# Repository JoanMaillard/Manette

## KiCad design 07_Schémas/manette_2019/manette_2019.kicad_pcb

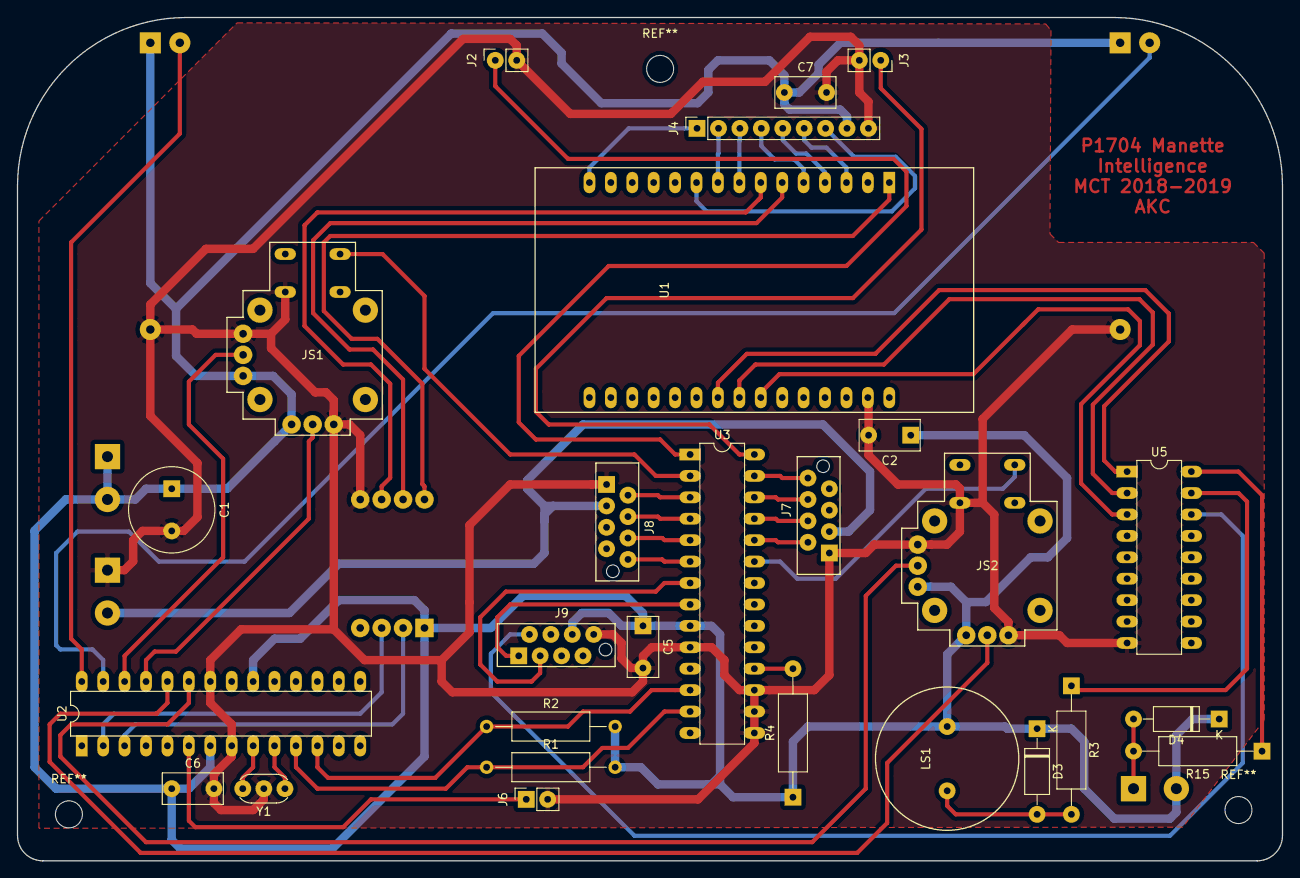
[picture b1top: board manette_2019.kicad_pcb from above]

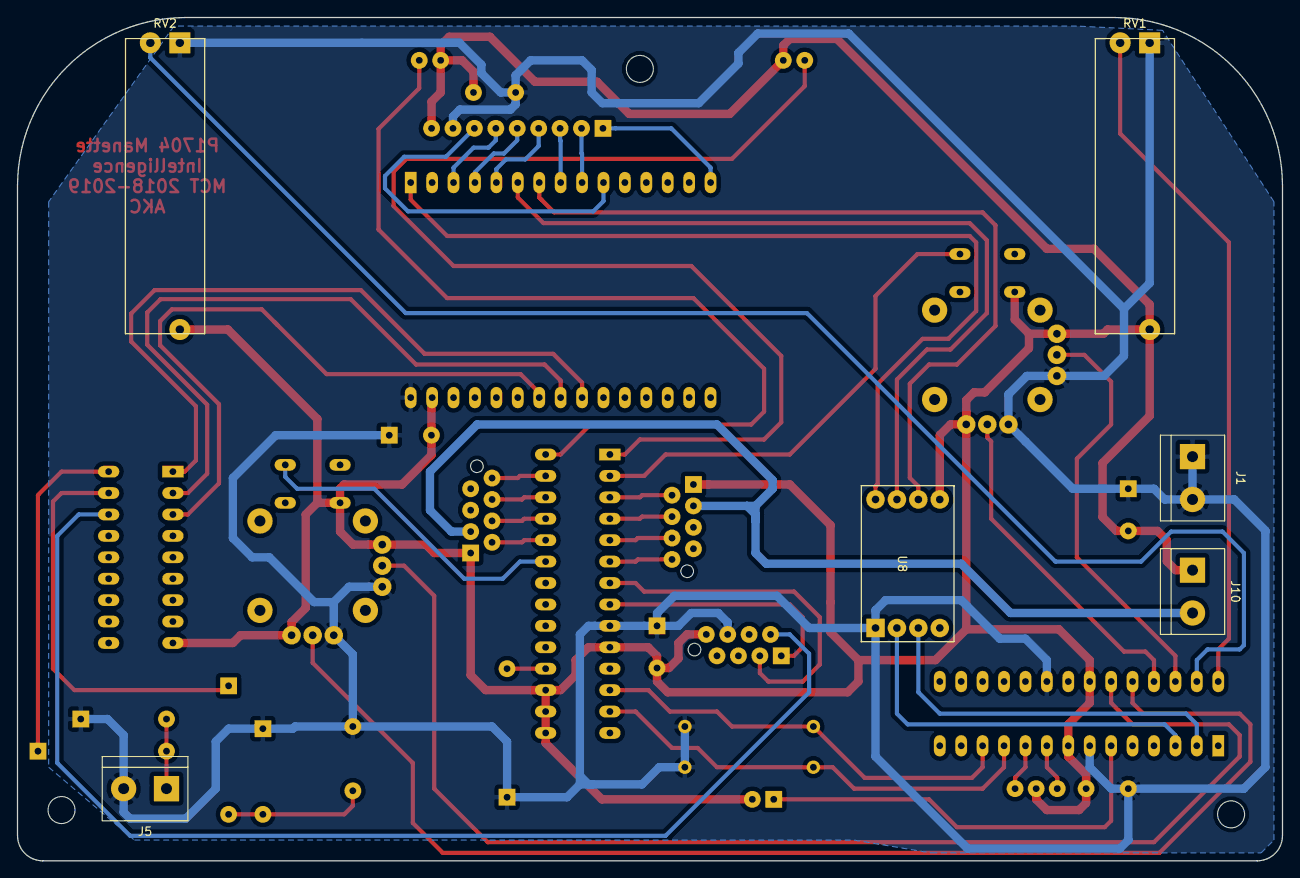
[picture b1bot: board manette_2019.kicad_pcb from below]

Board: 2 copper layers, 150.0 x 100.0 mm, 33 parts (6 on the bottom side), 49 nets.

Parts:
C1: C; C_Radial_D10.0mm_H20.0mm_P5.00mm
C2, C5, C6, C7: C; C_Rect_L7.0mm_W3.5mm_P5.00mm
D3, D4: D; D_A-405_P10.16mm_Horizontal
J1: Vcc; TerminalBlock_bornier-2_P5.08mm
J2: L_Bumper; PinSocket_1x02_P2.54mm_Vertical
J3: R_Bumper; PinSocket_1x02_P2.54mm_Vertical
J4: OLED_Display; PinSocket_1x09_P2.54mm_Vertical
J5: Rumble; TerminalBlock_bornier-2_P5.08mm
J6: Calib; PinSocket_1x02_P2.54mm_Vertical
J7: Conn_R_Button; Conn_8
J8: Conn_L_Button; Conn_8
J9: Conn_Middle_PCB; Conn_8
J10: Alim_LED; TerminalBlock_bornier-2_P5.08mm
JS1: Joystick_Left; Joystick_RSF_2-axis
JS2: Joystick_Right; Joystick_RSF_2-axis
LS1: Speaker; Buzzer_T135
R1, R2, R3, R4, R15: R; R_Axial_DIN0309_L9.0mm_D3.2mm_P15.24mm_Horizontal
RV1: L_POT; Potentiomètre linéaire
RV2: R_POT; Potentiomètre linéaire
U1: ESP32
U2: ATmega328-PU; DIP-28_W7.62mm
U3: MCP23017; DIP-28_W7.62mm
U5: ULN2803A; DIP-18_W7.62mm
U8: PCA9306
Y1: Resonator; Resonator-3Pin_W6.0mm_H3.0mm

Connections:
+3.3V: U1.1, U8.8
+5V: C1.1, C2.1, C5.1, C6.1, C7.1, D3.1, D4.1, J1.1, J1.2, J4.8, J5.2, J9.6, JS1.1, JS1.4, JS2.1, JS2.4, LS1.2, R1.2, R2.2, R4.1, RV1.1, RV2.1, U1.30, U2.7, U2.20, U3.9, U8.1
Button_A: J7.2, U3.24
Button_B: J7.8, U3.27
Button_DOWN: J8.6, U3.5
Button_LEFT: J8.8, U3.6
Button_RIGHT: J8.4, U3.4
Button_SELECT: J9.1, U3.8
Button_START: J9.3, U3.7
Button_UP: J8.2, U3.3
Button_X: J7.4, U3.25
Button_Y: J7.6, U3.26
Buzzer: U1.23, U5.2
Calib: J6.1, U2.6
Conn_LED_On: J9.2, U5.16
Connected: U1.24, U5.3
DC: J4.3, U1.8
GND: C1.2, C2.2, C5.2, C6.2, C7.2, J2.2, J3.2, J4.9, J6.2, J7.1, J8.1, J9.8, J10.1, JS1.3, JS1.6, JS1.9, JS2.3, JS2.6, JS2.9, RV1.3, RV2.3, U1.29, U2.8, U2.22, U3.10, U3.15, U3.16, U3.17, U5.9, U8.5, Y1.2
L_Bumper: J2.1, U3.1
L_joystick_analog_x: JS1.2, U2.26
L_joystick_analog_y: JS1.5, U2.25
L_trigger: RV1.2, U2.28
Left_joystick_button: JS1.8, U3.2
MISO: J4.7, U1.10
MOSI: J4.1, U1.15
unnamed: D3.2, LS1.1, R3.2
unnamed: D4.2, J5.1, R15.2
unnamed: R3.1, U5.17
unnamed: R4.2, U3.18
unnamed: R15.1, U5.18
unnamed: U2.9, Y1.3
unnamed: U2.10, Y1.1
OLEDCS: J4.5, U1.4
RESET: J4.4, U1.5
RX_Atmega: U2.2, U8.3
RX_ESP32: U1.6, U8.7
R_Bumper: J3.1, U3.28
R_joystick_analog_x: JS2.2, U2.23
R_joystick_analog_y: JS2.5, U2.24
R_trigger: RV2.2, U2.27
Right_joystick_button: JS2.8, U3.23
Rumble: U1.22, U5.1
SCK: J4.2, U1.9
SCL: R2.1, U2.12, U3.12
SDA: R1.1, U2.11, U3.13
SDCS: J4.6, U1.3
TX_Atmega: U2.3, U8.2
TX_ESP32: U1.7, U8.6
VCC_LED: J7.3, J8.3, J10.2

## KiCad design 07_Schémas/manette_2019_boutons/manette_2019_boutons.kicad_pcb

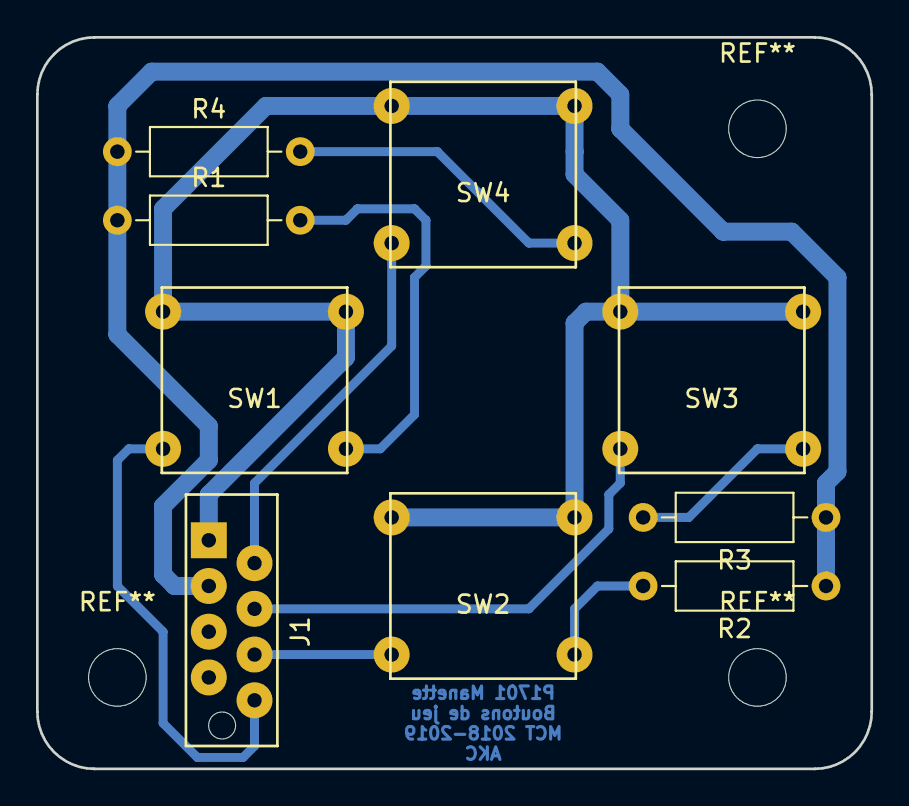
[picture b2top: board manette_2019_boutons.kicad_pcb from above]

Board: 2 copper layers, 46.4 x 40.6 mm, 9 parts (0 on the bottom side), 10 nets.

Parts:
J1: Conn_bouton; Conn_8
R1, R2, R3, R4: R; R_Axial_DIN0207_L6.3mm_D2.5mm_P10.16mm_Horizontal
SW1: Bouton_1; Bouton_MEC
SW2: Bouton_2; Bouton_MEC
SW3: Bouton_3; Bouton_MEC
SW4: Bouton_4; Bouton_MEC

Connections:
Bouton_Bas: J1.6, SW2.4
Bouton_Droite: J1.4, SW3.4
Bouton_Gauche: J1.8, SW1.4
Bouton_Haut: J1.2, SW4.4
GND: J1.1, SW1.1, SW1.2, SW2.1, SW2.2, SW3.1, SW3.2, SW4.1, SW4.2
unnamed: R1.2, SW1.3
unnamed: R2.2, SW2.3
unnamed: R3.2, SW3.3
unnamed: R4.2, SW4.3
Vcc_LED: J1.3, R1.1, R2.1, R3.1, R4.1

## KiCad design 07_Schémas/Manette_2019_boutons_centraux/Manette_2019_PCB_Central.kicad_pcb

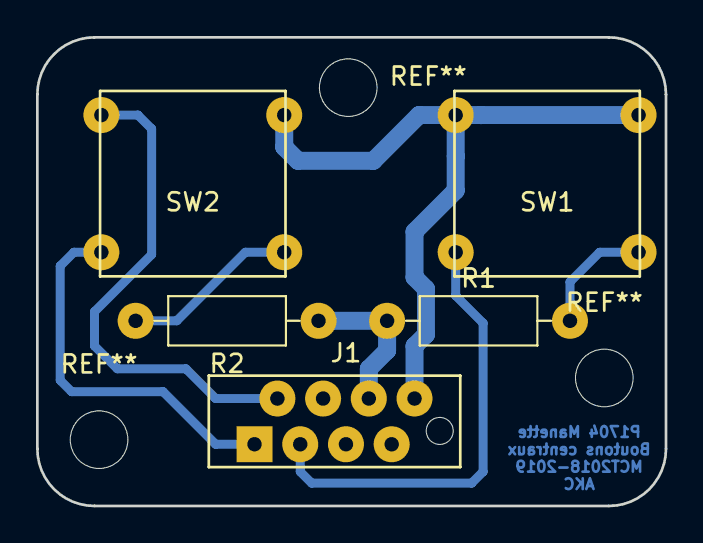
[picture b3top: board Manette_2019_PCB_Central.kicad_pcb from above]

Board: 2 copper layers, 34.9 x 26.0 mm, 5 parts (0 on the bottom side), 7 nets.

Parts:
J1: Conn_Middle_PCB; Conn_8
R1, R2: R; R_Axial_DIN0207_L6.3mm_D2.5mm_P10.16mm_Horizontal
SW1: Button_Start; Bouton_MEC
SW2: Button_Select; Bouton_MEC

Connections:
+5V: J1.6, R1.1, R2.1
Conn_LED_On: J1.2, SW2.2
GND: J1.8, SW1.1, SW1.2, SW2.1
unnamed: R1.2, SW1.3
unnamed: R2.2, SW2.3
button_SELECT: J1.1, SW2.4
button_START: J1.3, SW1.4

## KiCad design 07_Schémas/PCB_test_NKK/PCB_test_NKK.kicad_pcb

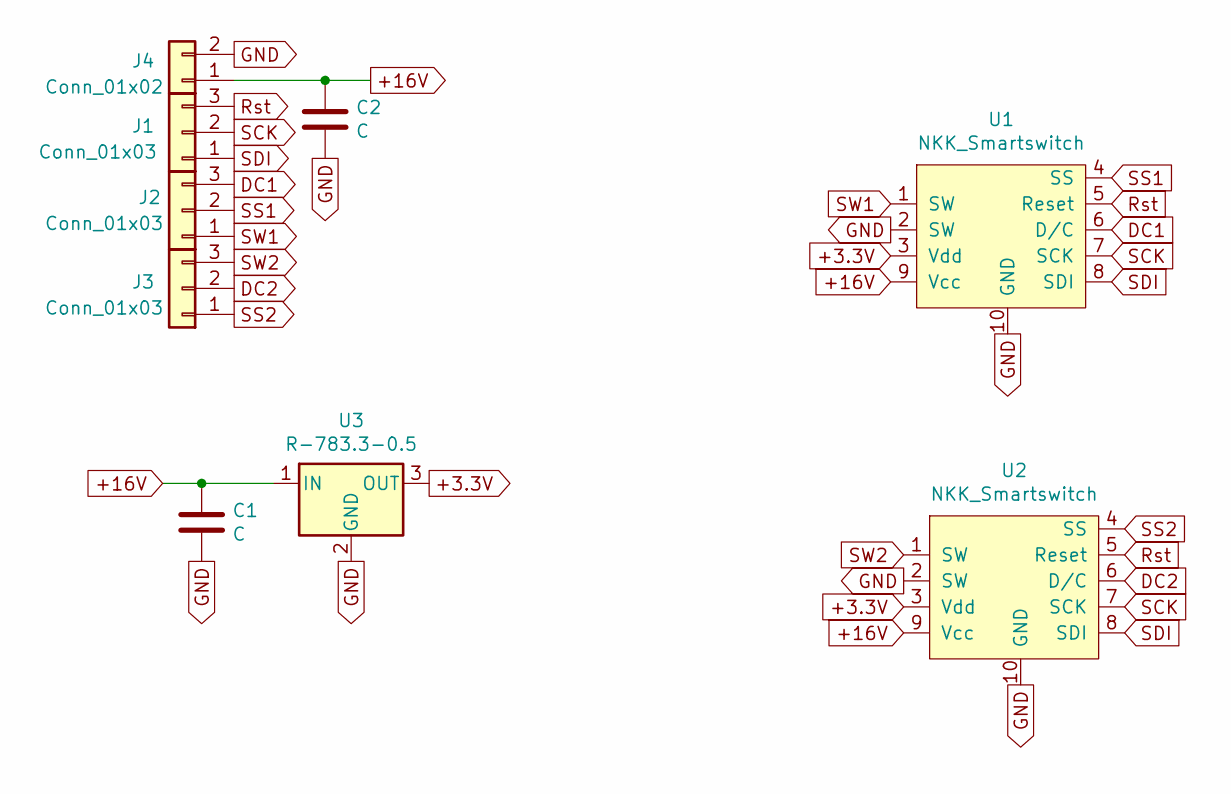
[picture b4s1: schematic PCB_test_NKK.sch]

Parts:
C1: C; C_Rect_L7.2mm_W3.5mm_P5.00mm_FKS2_FKP2_MKS2_MKP2
C2: C; CP_Radial_D10.0mm_P5.00mm
J1, J2, J3: Conn_01x03; TerminalBlock_Phoenix_MPT-0,5-3-2.54_1x03_P2.54mm_Horizontal
J4: Conn_01x02; TerminalBlock_Phoenix_MPT-0,5-2-2.54_1x02_P2.54mm_Horizontal
U1, U2: NKK_Smartswitch; NKK_Switch
U3: R-783.3-0.5; Converter_DCDC_RECOM_R-78E-0.5_THT

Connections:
+3.3V: U1.3 (Vdd), U2.3 (Vdd), U3.3 (OUT)
+16V: C1.1, C2.1, J4.1, U1.9 (Vcc), U2.9 (Vcc), U3.1 (IN)
DC1: J2.3, U1.6 (D/C)
DC2: J3.2, U2.6 (D/C)
GND: C1.2, C2.2, J4.2, U1.2 (SW), U1.10 (GND), U2.2 (SW), U2.10 (GND), U3.2 (GND)
Rst: J1.3, U1.5 (Reset), U2.5 (Reset)
SCK: J1.2, U1.7 (SCK), U2.7 (SCK)
SDI: J1.1, U1.8 (SDI), U2.8 (SDI)
SS1: J2.2, U1.4 (SS)
SS2: J3.1, U2.4 (SS)
SW1: J2.1, U1.1 (SW)
SW2: J3.3, U2.1 (SW)

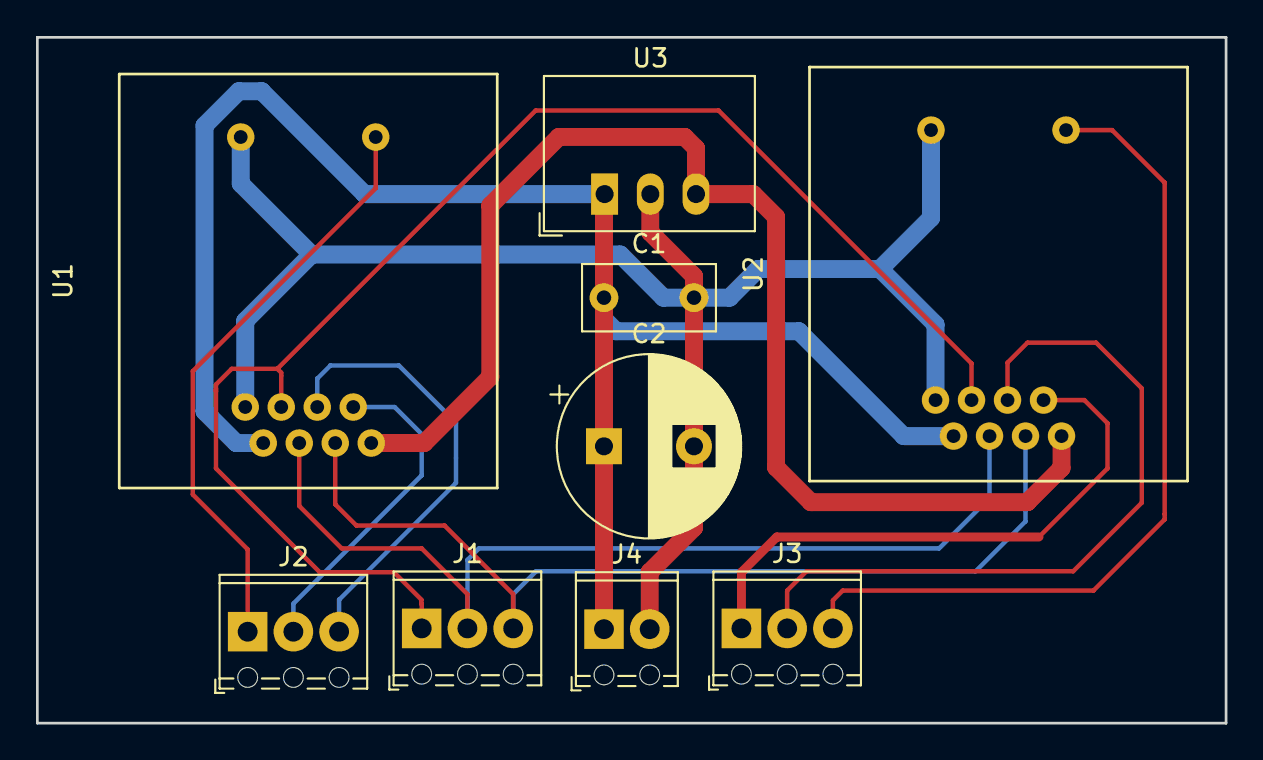
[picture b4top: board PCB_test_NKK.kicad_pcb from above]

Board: 2 copper layers, 66.0 x 38.1 mm, 9 parts (0 on the bottom side), 12 nets.

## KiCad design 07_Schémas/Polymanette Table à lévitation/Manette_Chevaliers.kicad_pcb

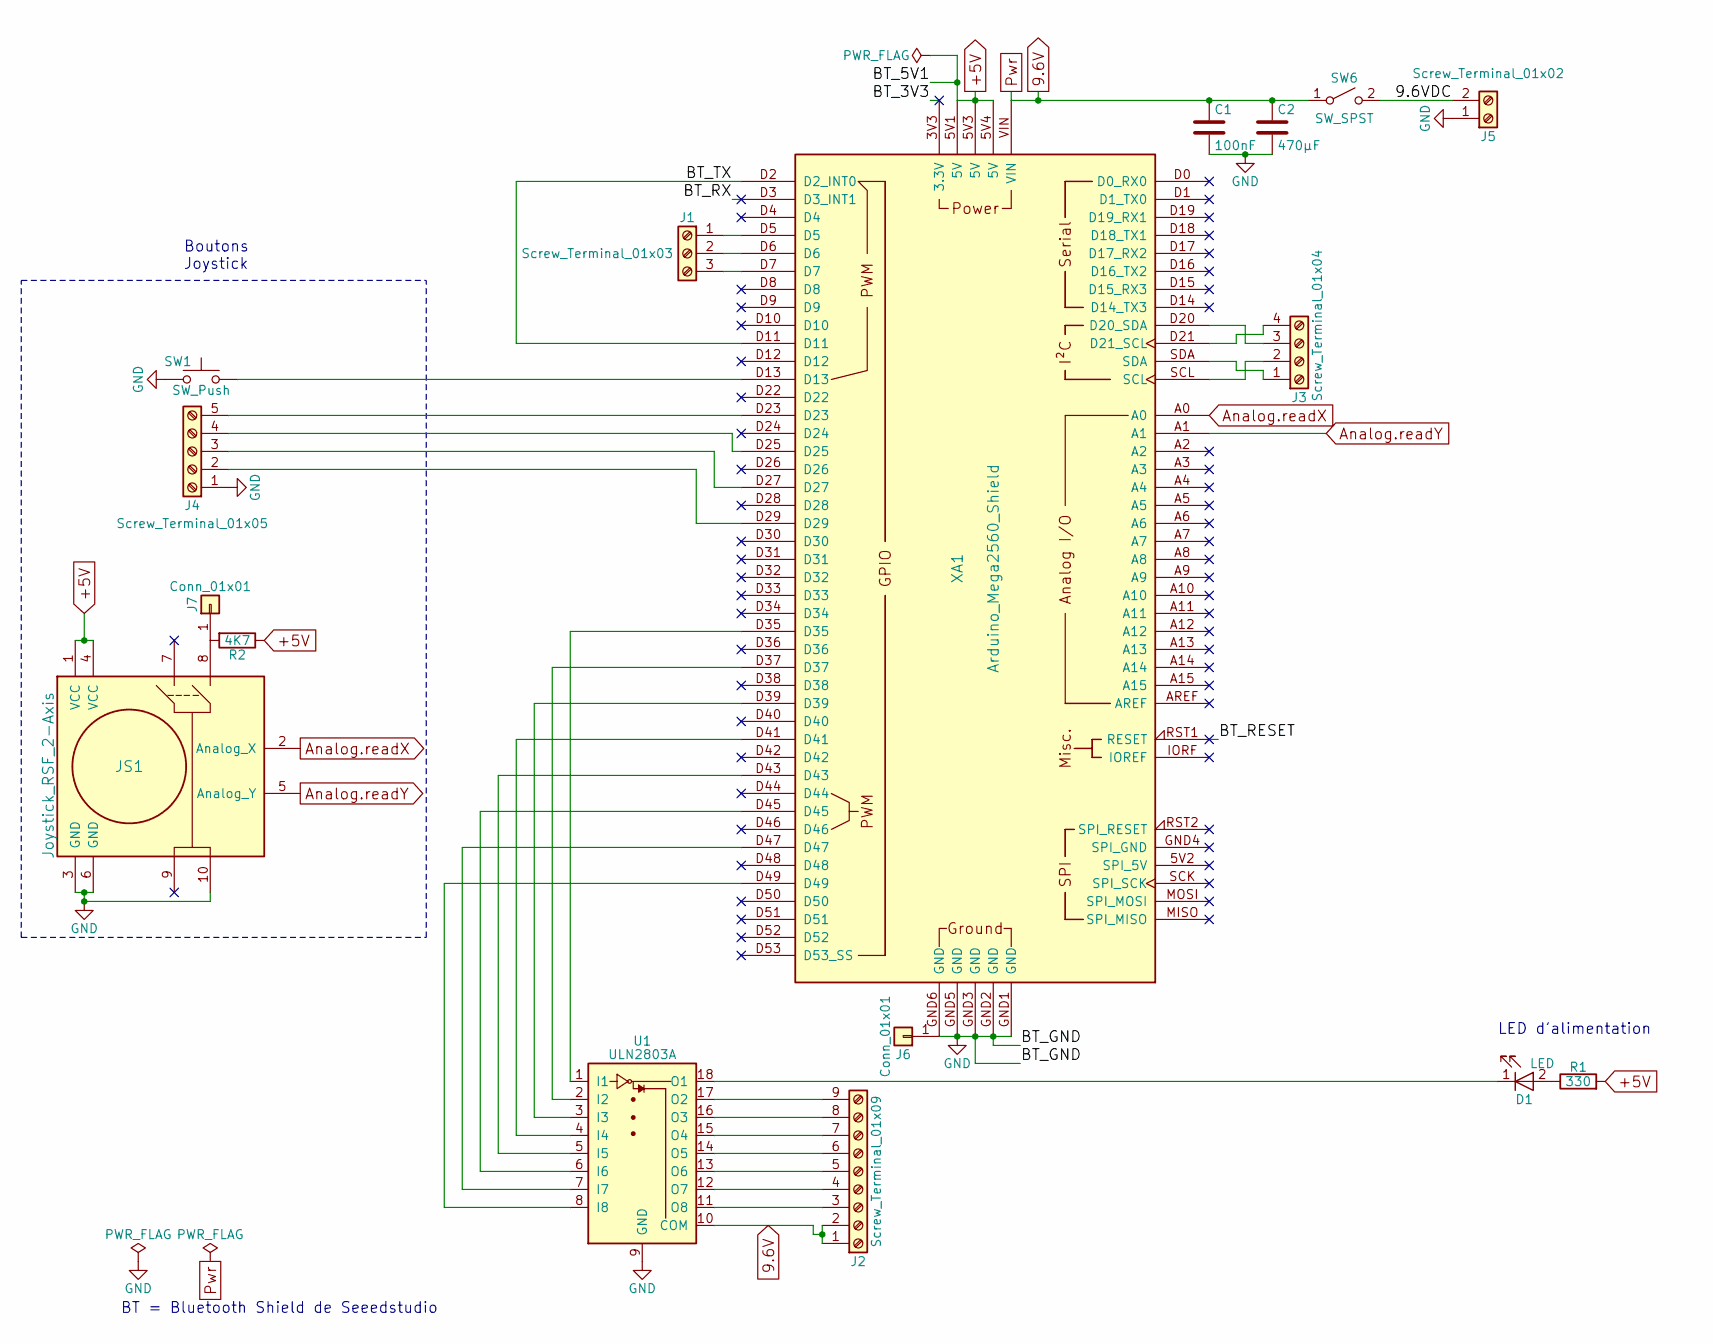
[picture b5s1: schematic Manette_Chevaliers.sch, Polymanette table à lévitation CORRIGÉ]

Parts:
C1: 100nF; C_Rect_L7.2mm_W2.5mm_P5.00mm_FKS2_FKP2_MKS2_MKP2
C2: 470µF; CP_Radial_Couchée_D10.0mm_P5.00mm
D1: LED; LED_D3.0mm
J1: Screw_Terminal_01x03; Screw_terminal_3_P2.54mm
J2: Screw_Terminal_01x09; Screw_terminal_3x3_P2.54mm
J3: Screw_Terminal_01x04; Screw_terminal_2x2_P2.54mm
J4: Screw_Terminal_01x05; Screw_terminal_2x3_P2.54mm
J5: Screw_Terminal_01x02; TerminalBlock_bornier-2_P5.08mm
J6, J7: Conn_01x01; Pad
JS1: Joystick_RSF_2-Axis; Joystick_RSF_2-axis
R1: 330; R_Axial_DIN0207_L6.3mm_D2.5mm_P10.16mm_Horizontal
R2: 4K7; R_Axial_DIN0207_L6.3mm_D2.5mm_P10.16mm_Horizontal
SW1: SW_Push; Switch_AS11CH
SW6: SW_SPST; Switch_AS11CH
U1: ULN2803A; ULN2803a
XA1: Arduino_Mega2560_Shield

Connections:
9.6V: C1.1, C2.1, J2.1, J2.2, SW6.1 (A), U1.10 (COM), XA1.VIN
+5V: JS1.1 (VCC), JS1.4 (VCC), R1.2, R2.1, XA1.5V1 (5V), XA1.5V3 (5V), XA1.5V4 (5V)
/9.6VDC: J5.2, SW6.2 (B)
/BT_3V3: XA1.3V3 (3.3V)
/BT_RESET: XA1.RST1 (RESET)
/BT_RX: XA1.D3 (D3_INT1)
/BT_TX: XA1.D2 (D2_INT0), XA1.D11
Analog.readX: JS1.2 (Analog_X), XA1.A0
Analog.readY: JS1.5 (Analog_Y), XA1.A1
GND: C1.2, C2.2, J4.1, J5.1, J6.1, JS1.3 (GND), JS1.6 (GND), JS1.10, SW1.2, U1.9 (GND), XA1.GND1 (GND), XA1.GND2 (GND), XA1.GND3 (GND), XA1.GND5 (GND), XA1.GND6 (GND)
unnamed: D1.1 (K), U1.18 (O1)
unnamed: D1.2 (A), R1.1
unnamed: J1.1, XA1.D5
unnamed: J1.2, XA1.D6
unnamed: J1.3, XA1.D7
unnamed: J2.3, U1.11 (O8)
unnamed: J2.4, U1.12 (O7)
unnamed: J2.5, U1.13 (O6)
unnamed: J2.6, U1.14 (O5)
unnamed: J2.7, U1.15 (O4)
unnamed: J2.8, U1.16 (O3)
unnamed: J2.9, U1.17 (O2)
unnamed: J3.1, XA1.SDA
unnamed: J3.2, XA1.SCL
unnamed: J3.3, XA1.D20 (D20_SDA)
unnamed: J3.4, XA1.D21 (D21_SCL)
unnamed: J4.2, XA1.D29
unnamed: J4.3, XA1.D27
unnamed: J4.4, XA1.D25
unnamed: J4.5, XA1.D23
unnamed: J7.1, JS1.8, R2.2
unnamed: SW1.1, XA1.D13
unnamed: U1.1 (I1), XA1.D35
unnamed: U1.2 (I2), XA1.D37
unnamed: U1.3 (I3), XA1.D39
unnamed: U1.4 (I4), XA1.D41
unnamed: U1.5 (I5), XA1.D43
unnamed: U1.6 (I6), XA1.D45
unnamed: U1.7 (I7), XA1.D47
unnamed: U1.8 (I8), XA1.D49

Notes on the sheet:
Boutons Joystick
BT = Bluetooth Shield de Seeedstudio
LED d'alimentation

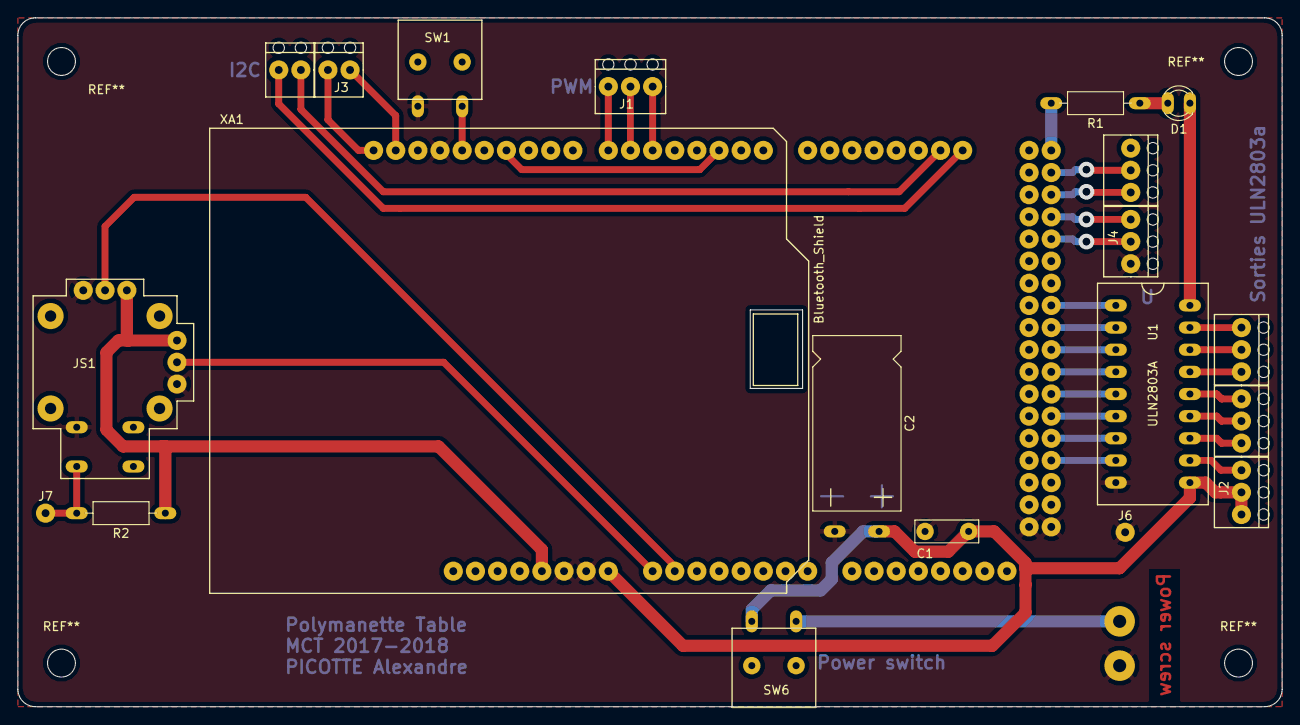
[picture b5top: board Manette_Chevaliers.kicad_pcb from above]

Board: 2 copper layers, 145.0 x 79.0 mm, 17 parts (1 on the bottom side), 37 nets.

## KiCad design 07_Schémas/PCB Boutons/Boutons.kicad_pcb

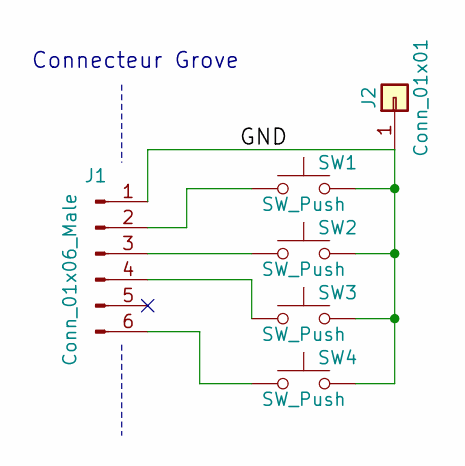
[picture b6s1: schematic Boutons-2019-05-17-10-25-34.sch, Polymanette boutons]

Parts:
J1: Conn_01x06_Male; Conn_Grove_6_pôles
J2: Conn_01x01; Pad
SW1, SW2, SW3, SW4: SW_Push; Switch_D6R

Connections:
/GND: J1.1, J2.1, SW1.2, SW2.2, SW3.2, SW4.2
unnamed: J1.2, SW1.1
unnamed: J1.3, SW2.1
unnamed: J1.4, SW3.1
unnamed: J1.6, SW4.1

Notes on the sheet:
Connecteur Grove

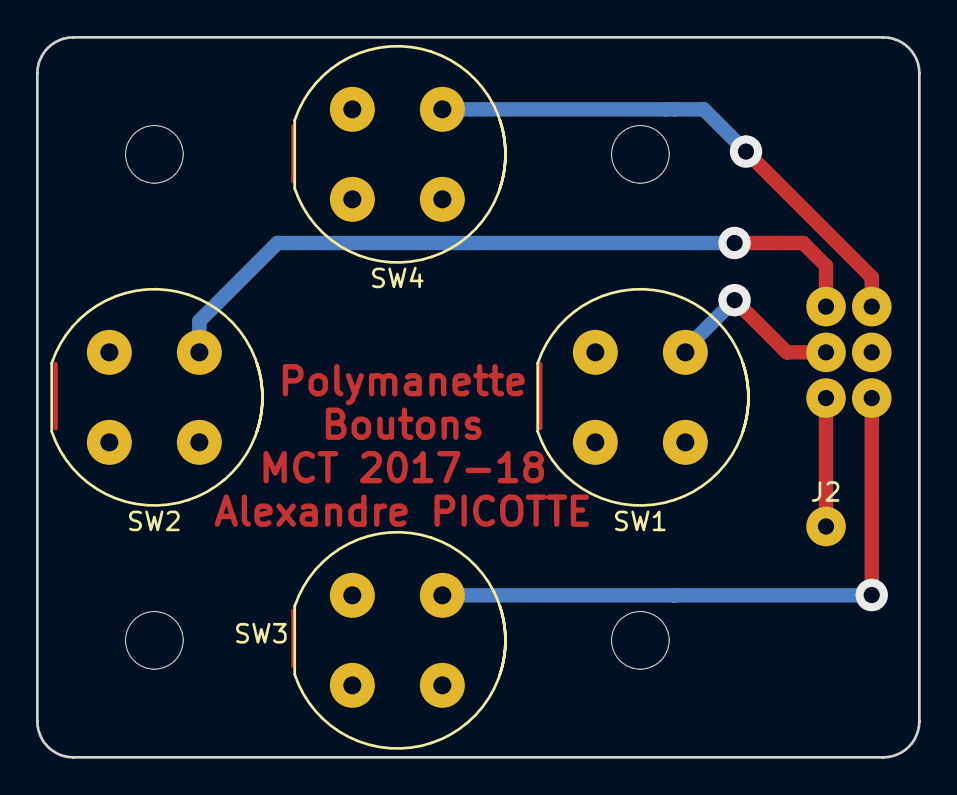
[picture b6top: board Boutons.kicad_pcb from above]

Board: 2 copper layers, 49.0 x 40.0 mm, 6 parts (1 on the bottom side), 5 nets.

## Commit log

2019-03-04 Initial commit
    Initial commit
2019-03-04 added résumé
    asdf
2019-03-04 schéma
2019-03-05 Code for serial communication testing
2019-03-05 Update journal, update MSProject sheet
2019-03-07 update schéma
2019-03-07 schéma update
2019-03-07 test code modified
    New code for 2 buttons and 1 potentiometer through Serial
2019-03-07 Optimization of test code (8 buttons to 1 byte)
2019-03-07 powerpoint
2019-03-07 update data rate test code
2019-03-07 Started schéma pour le test bench, cahier des charges
2019-03-11 update project file, receiver
2019-03-11 Cahier des charges
2019-03-11 update txt cahier des charges, plan projet MS Project
2019-03-12 added BT + PJON test code, doc refs, sub-diagram for BT comm
2019-03-12 Merge-fix commit
2019-03-12 Update plan de projet
2019-03-14 Cahier des charges intergroupe; save as XML des documents word
2019-03-14 Converted word documents to html
2019-03-14 Redo last
2019-03-15 docx update
2019-03-19 Update test_serial_sender.ino
    Added calibration routine
2019-03-21 Added per-direction calibration for good axis centering
2019-03-22 correct esp device names
2019-03-22 changes to comm code
2019-03-25 update MSP
2019-03-25 schema
2019-03-25 file movement
2019-03-25 update schema
2019-03-25 update code BT - working copy
2019-03-26 update BT code, journal, résumé
2019-03-26 ble code
2019-03-26 update code ESP for BT 33Hz
2019-03-26 Included serial receiver into BLE transmission
2019-03-28 Added two-way on BLE; sub-diagram update
2019-03-28 update receiver side
2019-04-01 update programmes
2019-04-02 update codes divers
2019-04-02 program corrections
2019-04-02 server and receiver change
2019-04-04 Update plan_projet_manette_2019.mpp
    quelques modifs à faire possiblement
2019-04-04 Update server code for latency reduction
2019-04-04 added a button
2019-04-08 added Troubleshooting latence
2019-04-08 moving files
2019-04-08 Move protocole communication BT
2019-04-08 move codes, delete PJON-related stuff
2019-04-08 Ajout librairies dans les dossiers de code; doc
2019-04-08 Added ESP tests tick chart
2019-04-11 finished pcb_nkk
2019-04-11 data gatherer update (for loops everywhere)
2019-04-29 started 3D
2019-05-07 Plans et data movement
2019-05-13 transfer mods
2019-05-17 Code de test boutons NKK
2019-05-23 finished program for knights and dragon displays
2019-05-23 3D et ppt esp32
2019-05-23 bonjour
2019-05-24 update accu data, journal de travail
2019-06-03 changed image renderer for Adafruit display
2019-06-03 Update codes manettes pour interfacer avec le code du groupe P1631
2019-06-04 documentation
2019-06-04 administratif
2019-06-04 Update codes (commentaires)
2019-06-06 Commentaire BLE_server.ino
2019-06-06 Update data_gatherer.ino commentaires
2019-06-10 BITCONNEEEEECT
2019-06-13 Adaptation code pour console rétro
2019-06-13 Correction BLE_client.ino
2019-06-13 Added 9th output byte BLE_server.ino
2019-06-13 Added NKK-format letters a-i
2019-06-13 Added appendix cahier des charges
2019-06-13 Commenting, parenthesis staging corrections
2019-06-14 added timeout handling
2019-06-17 mod 3d
2019-06-18 update code
2019-06-24 update journal
2019-06-27 creation poster
2019-06-28 code manettes arcade
2019-06-29 Update data_gatherer.ino
    Added remapping des boutons pour correspondre à la manette breadboard
2019-06-29 update code pour manette universelle
